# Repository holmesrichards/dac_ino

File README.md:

# dac/ino

This is a pair of boards and corresponding library which provide CV and gate I/O for an Arduino Nano. It is derived from [shaduzlabs/synapse](https://github.com/shaduzlabs/synapse), and there are obvious similarities to [ArdCore](http://20objects.com/ardcore/), but there are significant differences with both. 

There are two boards, dac/ino and dac/ino lite.

Differences between these and Synapse are:

- Board design with space for Arduino Nano, instead of as Uno style shield
- No on-board jacks — pads for Molex or pin connectors (or direct soldering) instead
- Simplification by eliminating software-controlled range selection
- Number of inputs and outputs is different
- dac/ino lite is battery powered and has 0–5 V output range, also uses Arduino Vcc as voltage reference

## Features
### dac/ino has
- 4 x control voltage inputs, 0 to 5V
- 2 x control voltage outputs, individually configurable as 0 to 5 V, 0 to 10 V, or -5 to 5 V via jumpers, with 12 bits of resolution
- 4 x gate inputs (with interrupt)
- 2 x gate outputs
- Additional inputs/outputs (direct connections to Arduino): 4 analog, 2 digital
- All above inputs/outputs connect via Molex connectors or solder pads, or via pin headers for daughterboards
- Voltage reference chip
- 1 x eurorack power connector (10 pin)

### dac/ino lite has
- 2 x control voltage outputs, 0 to 5 V, with 12 bits of resolution
- 1 x gate output
- Additional inputs/outputs (direct connections to Arduino): 4 analog, 2 digital
- All above inputs/outputs connect via Molex connectors or solder pads
- 6–12 V battery or unipolar power supply

## Compatible Arduinos
The PCB layout is for an Arduino Nano (5V).

## Dependencies
- [DirectIO](https://github.com/mmarchetti/DirectIO), for fast digital pin access

## Respository
- KiCad format schematics and PCB layouts, and Arduino library and example sketches, may be found at [https://github.com/holmesrichards/dac_ino](https://github.com/holmesrichards/dac_ino).

- [Build notes](docs/Build_notes.md)
- [dac/ino schematic](docs/dac_ino.pdf) (A bit confusing because the repetitive parts of the circuit are handled with KiCad heirarchical pages, so you have lots of pages with only a few components on each.)

- [dac/ino PCB layout](docs/dac_ino_pcb.pdf)

- [dac/ino BOM](docs/dac_ino_bom.md)

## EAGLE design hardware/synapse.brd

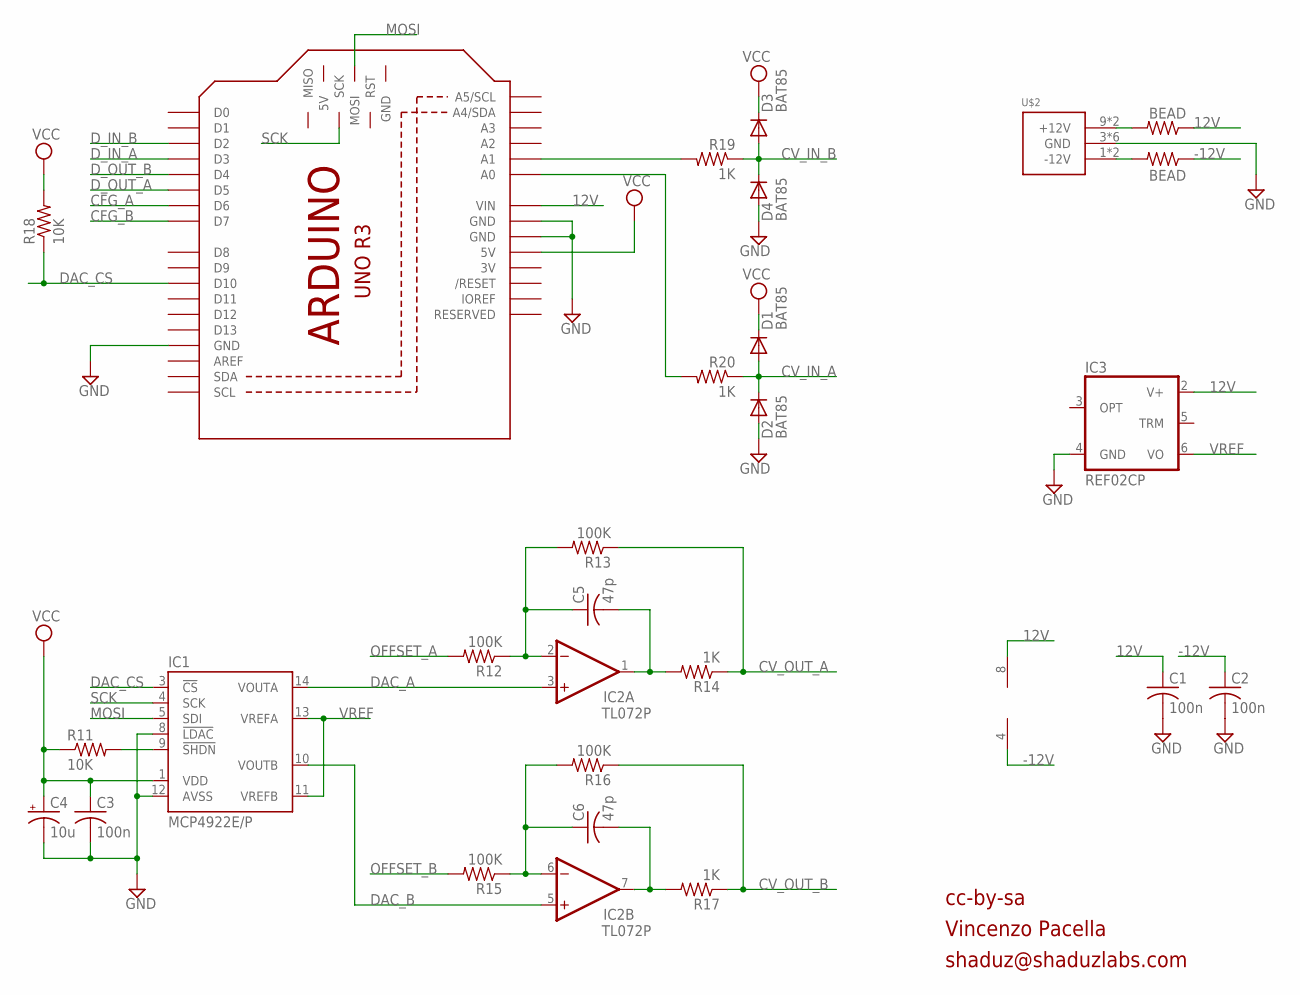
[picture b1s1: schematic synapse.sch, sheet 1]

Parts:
C1, C2, C3: 100n; C025-025X050
C4: 10u; E2-5
C5, C6: 47p; C025-025X050
D1, D2, D3, D4: BAT85; D-5
IC1: MCP4922E/P; DIL14
IC2: TL072P; DIL08
IC3: REF02CP; DIL08
M1: ARDUINO_R3_ICSP; ARDUINOR3_ICSP
R11, R18: 10K; 0204/7
R12, R13, R15, R16: 100K; 0204/7
R14, R17, R19, R20: 1K; 0204/7
R21, R24: BEAD; 0204/7
U$2: POWER_SIMPLE10; POWER_10

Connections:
3V: M1.3V
12V: C1.1, IC2.8 (V+), IC3.2 (V+), M1.VIN, R21.1
-12V: C2.1, IC2.4 (V-), R24.1
CFG_A: M1.D6; also elsewhere on the board
CFG_B: M1.D7; also elsewhere on the board
CV_IN_A: D1.A, D2.C, R20.1; also elsewhere on the board
CV_IN_B: D3.A, D4.C, R19.1; also elsewhere on the board
CV_OUT_A: R13.1, R14.1; also elsewhere on the board
CV_OUT_B: R16.1, R17.1; also elsewhere on the board
DAC_A: IC1.14 (VOUTA), IC2.3 (+IN)
DAC_B: IC1.10 (VOUTB), IC2.5 (+IN)
DAC_CS: IC1.3 (!CS!), M1.D10, R18.1
D_IN_A: M1.D3; also elsewhere on the board
D_IN_B: M1.D2; also elsewhere on the board
D_OUT_A: M1.D5; also elsewhere on the board
D_OUT_B: M1.D4; also elsewhere on the board
GND: C1.2, C2.2, C3.2, C4.-, D2.A, D4.A, IC1.8 (!LDAC!), IC1.12 (AVSS), IC3.4 (GND), M1.GND, M1.GND@1 (GND), M1.GND@3 (GND), U$2.3 (GND), U$2.4 (GND), U$2.5 (GND), U$2.6 (GND), U$2.7 (GND), U$2.8 (GND); also elsewhere on the board
MOSI: IC1.5 (SDI), M1.MOSI
unnamed: M1.A1, R19.2
unnamed: IC1.9 (!SHDN!), R11.2
unnamed: R21.2, U$2.9 (+12V), U$2.10 (+12V)
unnamed: R24.2, U$2.1 (-12V), U$2.2 (-12V)
unnamed: M1.A0, R20.2
unnamed: C5.1, IC2.2 (-IN), R12.1, R13.2
unnamed: C6.1, IC2.6 (-IN), R15.1, R16.2
unnamed: C5.2, IC2.1 (OUT), R14.2
unnamed: C6.2, IC2.7 (OUT), R17.2
OFFSET_A: R12.2; also elsewhere on the board
OFFSET_B: R15.2; also elsewhere on the board
SCK: IC1.4 (SCK), M1.SCK
VCC: C3.1, C4.+, D1.C, D3.C, IC1.1 (VDD), M1.5V, R11.1, R18.2; also elsewhere on the board
VREF: IC1.11 (VREFB), IC1.13 (VREFA), IC3.6 (VO); also elsewhere on the board

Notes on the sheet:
cc-by-sa
Vincenzo Pacella
shaduz@shaduzlabs.com

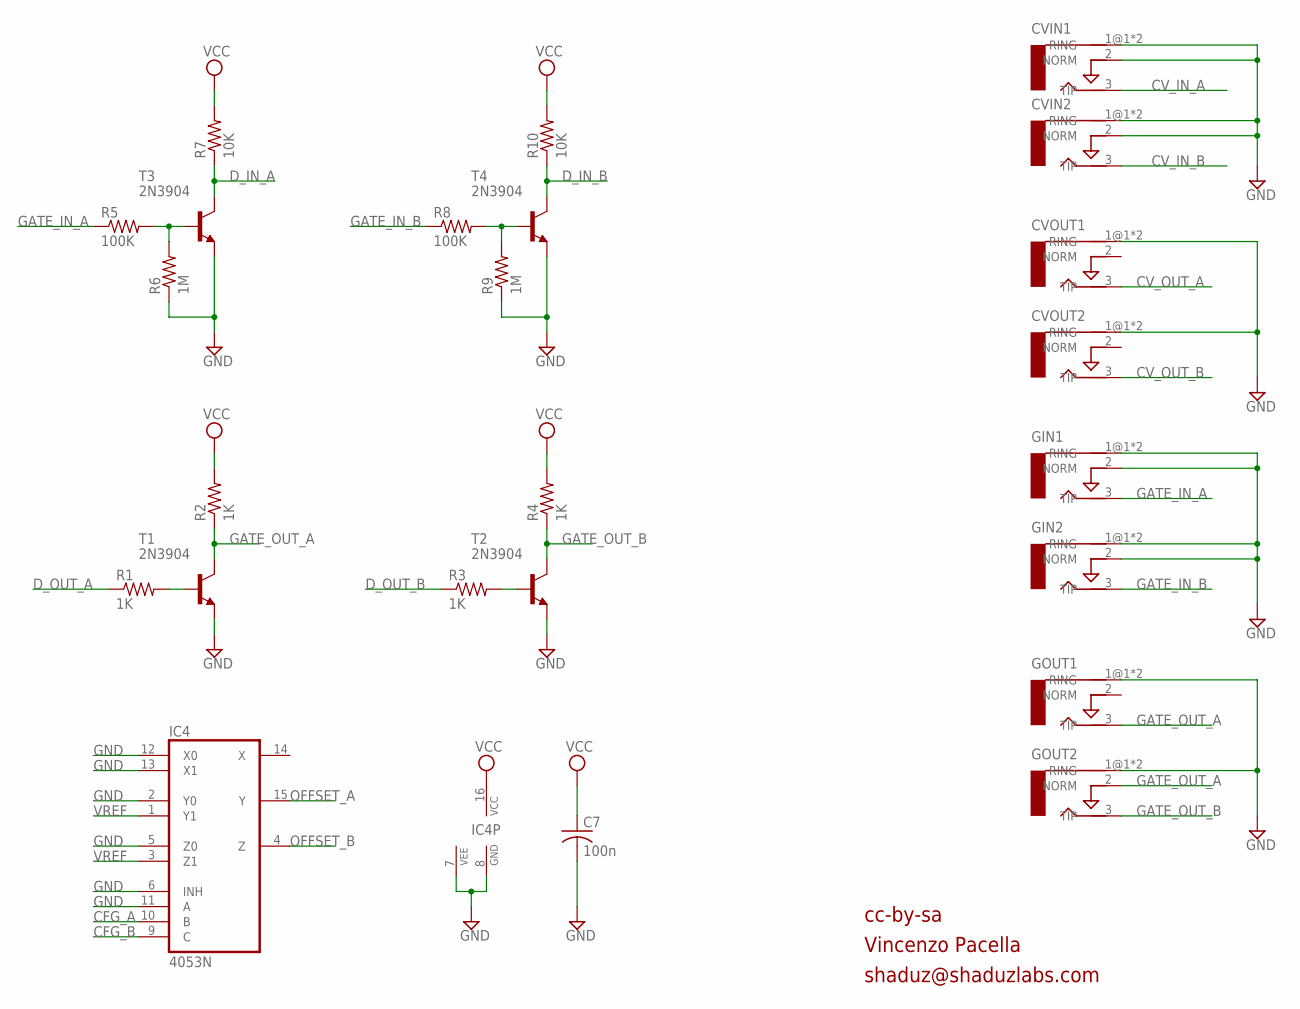
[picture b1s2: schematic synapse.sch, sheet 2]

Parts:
C7: 100n; C025-025X050
CVIN1, CVIN2: AUDIO-JACKERTHENVAR; ERTHENVAR-JACK
CVOUT1, CVOUT2: AUDIO-JACKERTHENVAR; ERTHENVAR-JACK
GIN1, GIN2: AUDIO-JACKERTHENVAR; ERTHENVAR-JACK
GOUT1, GOUT2: AUDIO-JACKERTHENVAR; ERTHENVAR-JACK
IC4: 4053N; DIL16
R1, R2, R3, R4: 1K; 0204/7
R5, R8: 100K; 0204/7
R6, R9: 1M; 0204/7
R7, R10: 10K; 0204/7
T1, T2, T3, T4: 2N3904; TO92-EBC

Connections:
CFG_A: IC4.10 (B); also elsewhere on the board
CFG_B: IC4.9 (C); also elsewhere on the board
CV_IN_A: CVIN1.3 (TIP); also elsewhere on the board
CV_IN_B: CVIN2.3 (TIP); also elsewhere on the board
CV_OUT_A: CVOUT1.3 (TIP); also elsewhere on the board
CV_OUT_B: CVOUT2.3 (TIP); also elsewhere on the board
D_IN_A: R7.1, T3.C; also elsewhere on the board
D_IN_B: R10.1, T4.C; also elsewhere on the board
D_OUT_A: R1.1; also elsewhere on the board
D_OUT_B: R3.1; also elsewhere on the board
GATE_IN_A: GIN1.3 (TIP), R5.1
GATE_IN_B: GIN2.3 (TIP), R8.1
GATE_OUT_A: GOUT1.3 (TIP), GOUT2.2 (NORM), R2.1, T1.C
GATE_OUT_B: GOUT2.3 (TIP), R4.1, T2.C
GND: C7.2, CVIN1.1@1 (RING), CVIN1.1@2 (RING), CVIN1.2 (NORM), CVIN2.1@1 (RING), CVIN2.1@2 (RING), CVIN2.2 (NORM), CVOUT1.1@1 (RING), CVOUT1.1@2 (RING), CVOUT2.1@1 (RING), CVOUT2.1@2 (RING), GIN1.1@1 (RING), GIN1.1@2 (RING), GIN1.2 (NORM), GIN2.1@1 (RING), GIN2.1@2 (RING), GIN2.2 (NORM), GOUT1.1@1 (RING), GOUT1.1@2 (RING), GOUT2.1@1 (RING), GOUT2.1@2 (RING), IC4.2 (Y0), IC4.5 (Z0), IC4.6 (INH), IC4.7 (VEE), IC4.8 (GND), IC4.11 (A), IC4.12 (X0), IC4.13 (X1), R6.1, R9.1, T1.E, T2.E, T3.E, T4.E; also elsewhere on the board
unnamed: R1.2, T1.B
unnamed: R3.2, T2.B
unnamed: R5.2, R6.2, T3.B
unnamed: R8.2, R9.2, T4.B
OFFSET_A: IC4.15 (Y); also elsewhere on the board
OFFSET_B: IC4.4 (Z); also elsewhere on the board
VCC: C7.1, IC4.16 (VCC), R2.2, R4.2, R7.2, R10.2; also elsewhere on the board
VREF: IC4.1 (Y1), IC4.3 (Z1); also elsewhere on the board

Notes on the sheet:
cc-by-sa
Vincenzo Pacella
shaduz@shaduzlabs.com

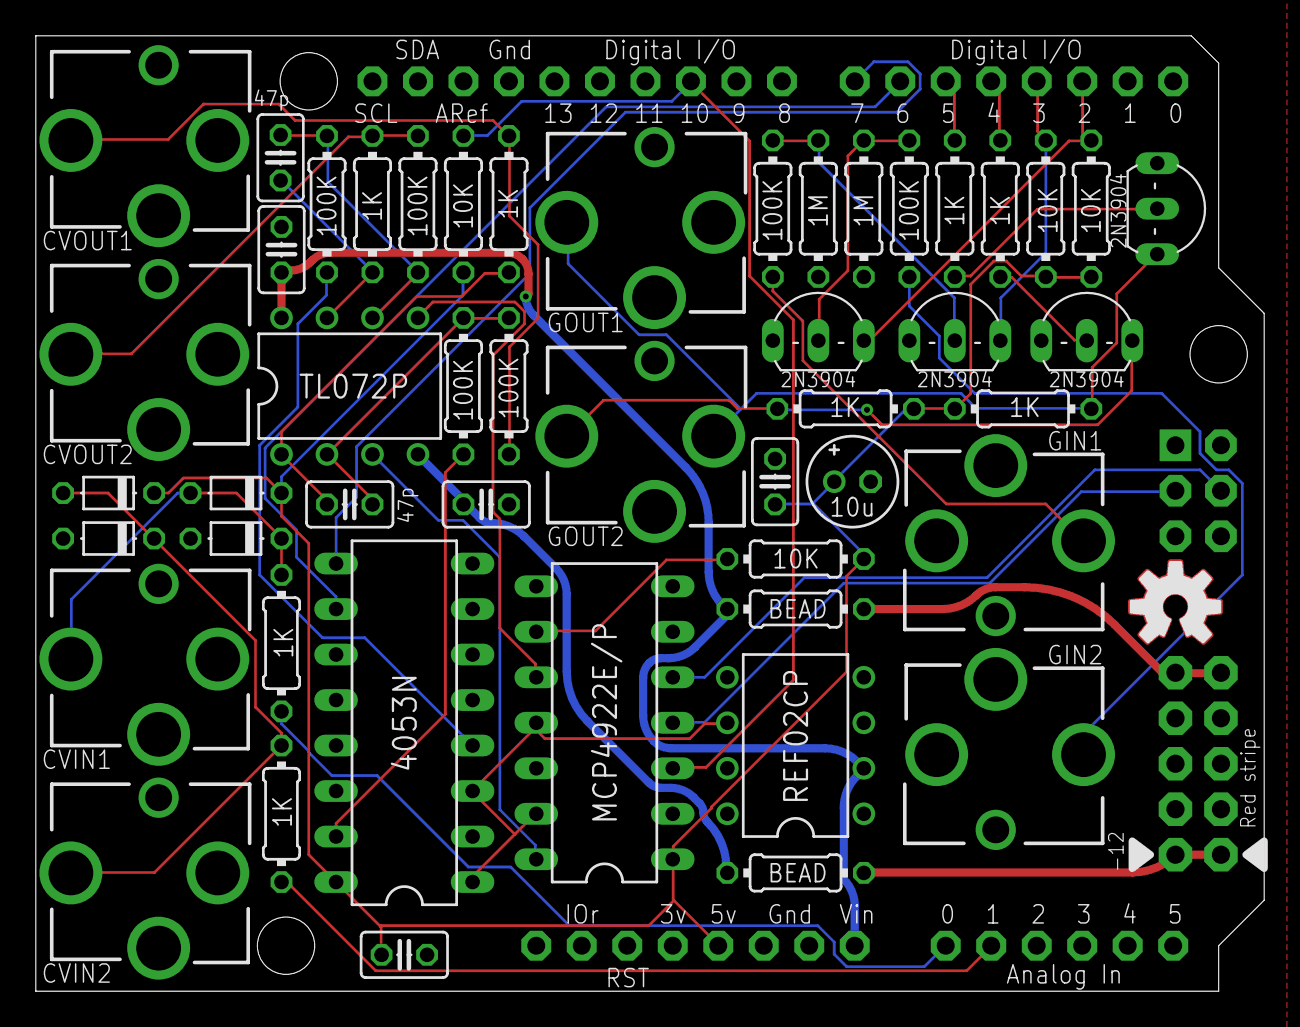
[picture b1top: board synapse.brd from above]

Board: 2 copper layers, 68.6 x 53.3 mm, 53 parts (1 on the bottom side), 39 nets.

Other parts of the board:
U$1: OSHWLOGO_TOP_0.2
U$3: OSHW-LOGO-M

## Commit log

2016-03-14 Update LICENSE for SW part
2016-03-14 Rename LICENSE to LICENSE-SW
2016-03-14 Create LICENSE-HW
2016-03-14 added SynapseTest.ino
2016-03-14 added TravisCI config
2016-03-14 added DirectIO dependency, updated TravisCI config and test project
2016-03-15 Update LICENSE-HW
2016-03-15 Updated schematic
2016-03-15 Interface updated
2016-03-15 updated keywords and Test file
2016-03-15 travis.yml: updated Arduino version to 1.6.8
2016-04-02 bugfixing
2016-09-20 added hardware project files, updated readme
2016-09-20 updater readme
2016-11-24 update travis configuration
2016-11-24 update list of compatible boards
2016-11-24 extend compatibility to non-AVR boards
2016-11-24 bump version (1.0.1)
2016-11-28 add .gitignore, update documentation
2016-11-28 add SynaBLE example
2016-11-29 renamed SynapseTest to Test
2016-12-16 SynaBLE example improved
2018-05-24 Backlink to CADLAB.io has been added.
2018-06-27 Use of angled 5x2 male strips
    Noticed you could use angled 5x2 strips for the IDC connector, so it would be possible to stack another header on top.
2018-07-04 Simple LFO example
2018-07-05 More examples
2018-07-09 Clock divide example
2018-07-09 Euclidian Trigger Sequencer
2018-07-09 Reset on Gate in B, CV controlled rotate
2018-07-09 Offset analog input pins
2018-07-09 Fix reset state check
2018-07-09 Fix pot value scaling
2018-07-09 Fix analog in pin numbers
2019-05-01 bump version (1.0.2)
    New examples added
2020-03-25 Original synapse hardware to orig_hardware; new KiCad files in hardware/dacarduino and hardware/dacarduino\ lite
2020-03-27 Revised layout, with voltage reference restored to dacarduino
2020-03-27 KiCad version of original hardware design
2020-03-27 Update to reflect Vref waffling
2020-03-27 Text files for some application ideas
2020-04-07 Revise switches plan
2020-04-07 PCB redraw; change op amp selection; revise power tags; move to spaceless directory
2020-04-12 Backlog of many changes
2020-04-12 Redid layout completely
2020-04-12 Additional inputs since the board has room
2020-04-13 .gitignore-extras
2020-04-13 Added hack area
2020-04-13 Added input pads
2020-04-13 remove file
2020-04-24 gitignore-extra
2020-04-24 Add multiplexer option
2020-04-24 Mention multiplexer option
2020-04-24 Revert multiplexer idea
2020-05-03 Post-prototype tweaks
2020-05-03 rm crufty file
2020-05-03 Minor copy edits
2020-05-04 Name change
2020-05-04 dac_ino Gerbers added
2020-05-04 Redo Gerbers
2020-05-04 Consistent annotation; BOMs
2020-05-04 Late silkscreen work
2020-05-04 Clarifying extra ins/outs
2020-05-09 Remove experimental artwork...
2020-05-15 Tweak fab layers and jack descriptions
2020-05-16 Revise and debug
2020-05-16 Correct output op amp connections
2020-05-17 Add headers for board coupling
2020-05-18 Final tweaks before fabbing revised board
2020-05-22 Separate in and out nomenclature. Add option to configure two gate pins as input or output.
2020-05-27 Pointer to repository
2020-05-27 New, modified, and removed examples
2020-05-28 Build notes
2020-05-28 Corrected output range for quantizer
2020-06-05 Rearrange PCB to make headers easier to use
2020-06-06 Reorient header
2020-06-06 Daughterboard template project
2020-06-07 Daughterboard edge adjustments, pdf and png
2020-06-07 Pin labels
2020-07-04 Chaos example
2020-07-04 Rearrange 8 pin Molex; convert footprints to AO versions and clean up silkscreen
2020-07-04 New Gerbers
2020-07-30 Newer Gerbers; correct silkscreen; note on silkscreen error
2020-07-31 Correct version
2020-08-24 Layer visibility
2020-08-25 Test program rewrite
2020-08-26 Nano interrupts are only pin 2, 3
2020-08-26 Build notes revisions
2020-08-28 Fix silkscreen error
2020-08-30 Docs directory with dac/ino schematics and layout
2020-08-30 BOM to docs directory
2020-08-30 Fix build notes file name
2020-08-30 BOM link in README
2020-09-08 Fix hopelessly out of date BOM
2020-09-27 Fix up some typos (that never should have made it to the repository!)
2020-11-28 Documentation updates, TODO
2021-01-02 Footprints updated
2021-01-17 Include lib table files
2021-01-17 Include dcm files
2021-01-24 Fix J1, J2 3D
2021-02-02 Ungarble labels
2021-02-19 Footprint update
2021-02-27 Fix C2 labeling
2021-03-13 Clarify silkscreen correction
2021-05-10 Less insane redraw of dac/ino lite schems

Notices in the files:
hardware/synapse.brd:
cc-by-sa Vincenzo Pacella - 04.2016 - Berlin / rev. 1.0
parts and their libraries:
SparkFun-Aesthetics: Licensing: Creative Commons ShareAlike 4.0 International - https://creativecommons.org/licenses/by-sa/4.0
